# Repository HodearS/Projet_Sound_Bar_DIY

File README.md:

# Projet_Sound_Bar_DIY

L'objectif de ce projet est de réaliser une barre de son DIY compatible Dolby Atmos.
Pour cela, la barre de son exploitera des architectures de chez Texas Instruments, à la fois pour le processeur audio et la carte d'amplification.

Travaux à réaliser :
- Ajouter un processeur prenant en charge la communication Bluetooth et Wi-Fi.
- Trouver une méthode permettant de basculer entre différentes sources audio.
- Concevoir l'architecture globale du projet (gestion des différentes cartes, intégration dans le boîtier, etc.).
- Concevoir la carte d’alimentation.
- Concevoir la carte d’interface.

Travaux réalisés :
- Reprise du schéma de la carte d’évaluation EVMK2GX de Texas Instruments pour le processeur 66AK2G12 → Processeur_Barre_Son_Avant_Projet.
- Reprise du schéma de la carte amplificateur audio TIDA-01414 utilisant les amplificateurs TPA3244 → Amplificateur_Audio_Avant_Projet.
- Reprise du schéma de la carte fille audio K2G → Audio_Carte_fille.

The objective of this project is to build a DIY Dolby Atmos-compatible soundbar.
To achieve this, the soundbar will use Texas Instruments architectures for both the audio processor and the amplifier board.

Tasks to be completed :
- Add a processor supporting Bluetooth and Wi-Fi communication.
- Find a method to switch between different audio sources.
- Design the overall architecture of the project (management of the different boards, integration into the case, etc.).
- Design the power supply board.
- Design the interface board.

Completed tasks :
-Recreated the schematic of the Texas Instruments evaluation board EVMK2GX for the 66AK2G12 processor → Processeur_Barre_Son_Avant_Projet.
-Recreated the schematic of the audio amplifier board TIDA-01414 using TPA3244 amplifiers → Amplificateur_Audio_Avant_Projet.
-Recreated the schematic of the K2G audio daughter card → Audio_Carte_fille.

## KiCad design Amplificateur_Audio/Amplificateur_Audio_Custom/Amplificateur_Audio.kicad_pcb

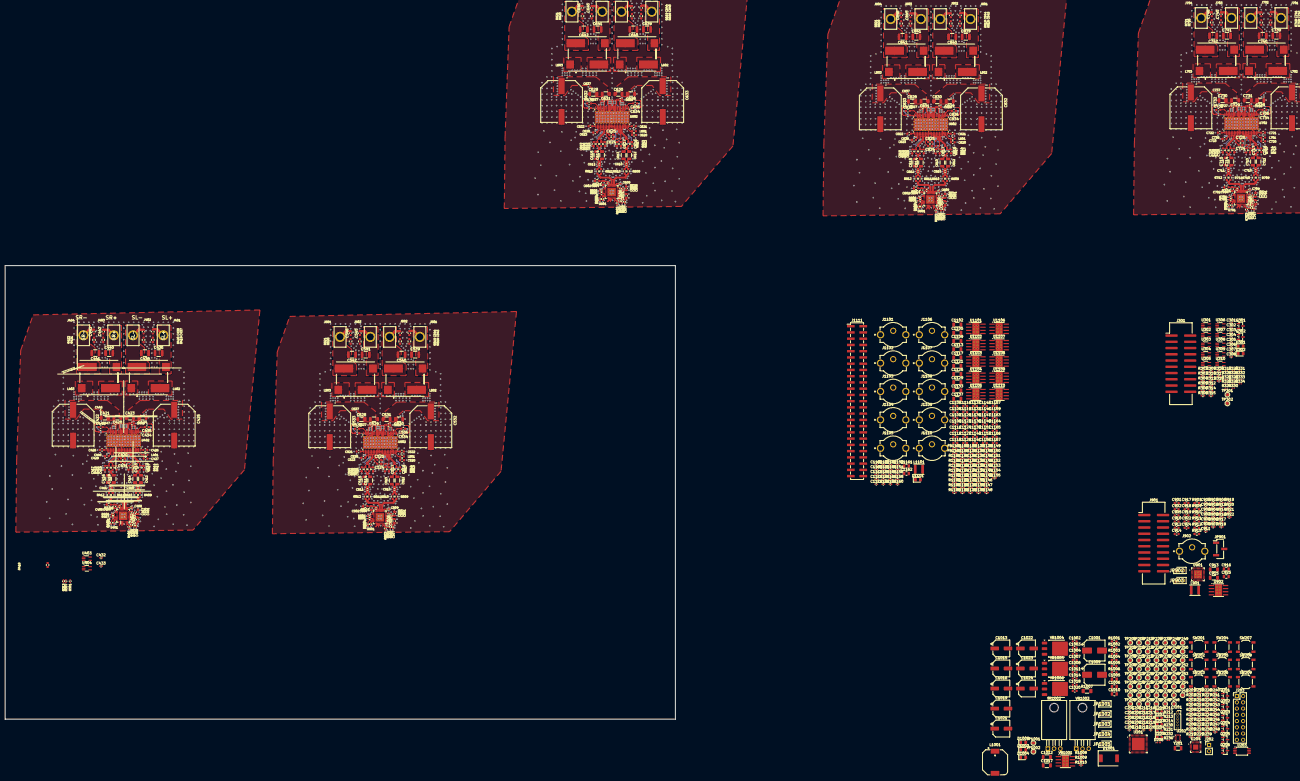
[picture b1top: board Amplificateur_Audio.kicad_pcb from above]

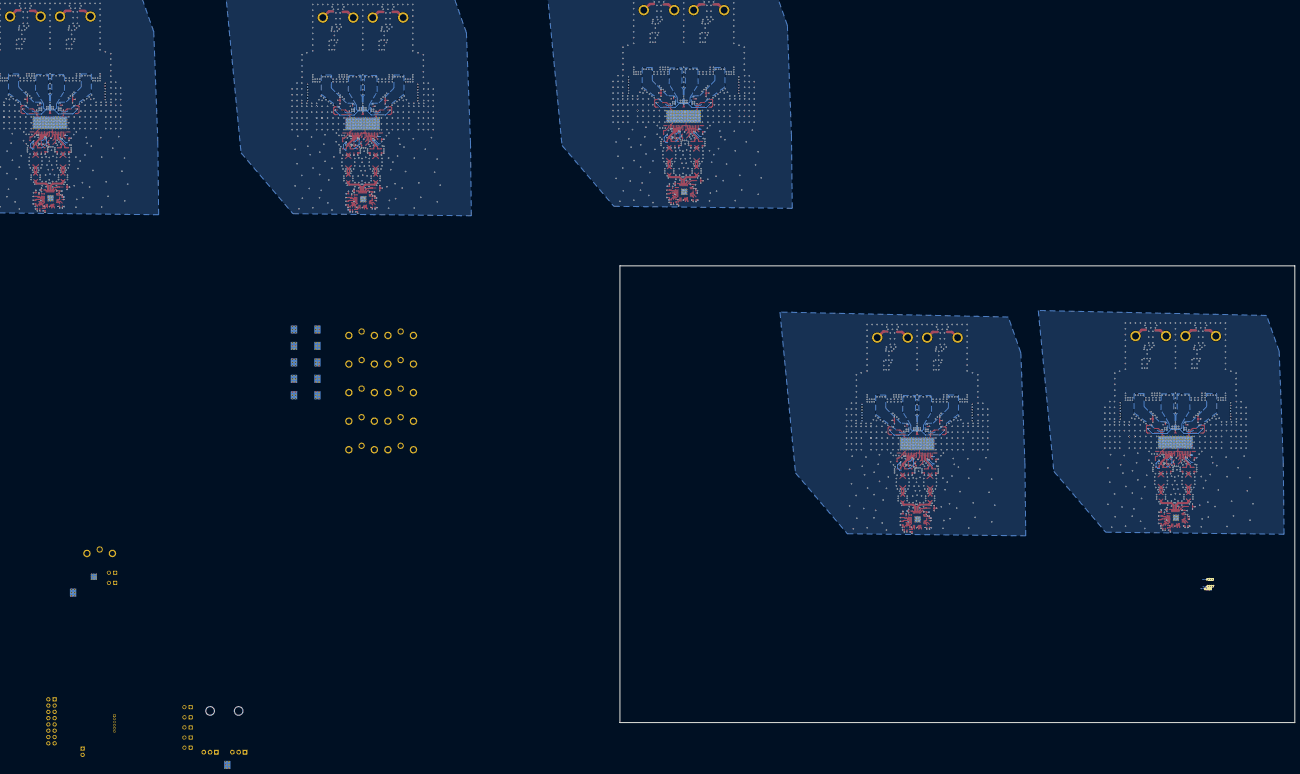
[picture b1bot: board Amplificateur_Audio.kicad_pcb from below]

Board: 4 copper layers, 272.5 x 184.4 mm, 847 parts (3 on the bottom side), 447 nets.

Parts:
C201, C202, C203, C204, C205, C206, C207, C208: 470pF; C_0402_1005Metric
C209, C301: 1uF; C_0402_1005Metric
C210, C211, C212, C213, C214, C215, C216, C302, C303, C304, C305, C306, C307, C308, C402, C404, C406, C409, C432, C433, C503, C504, C506, C507, C603, C604, C606, C607, C703, C704, C706, C707, C803, C804, C806, C807, C903, C904, C906, C908, C1101, C1106, C1110, C1114, C1118, C1122, C1126, C1130, C1134, C1138, C1142, C1144, C1146, C1148, C1150, C1152, C1154, C1156, C1158, C1160: 0.1uF; C_0402_1005Metric
C217, C218: 2200pF; C_0402_1005Metric
C219, C220: 12pF; C_0402_1005Metric
C401, C403, C405, C501, C502, C505, C601, C602, C605, C701, C702, C705, C801, C802, C805, C901, C902, C905, C914, C918, C922, C1141, C1143, C1145, C1147, C1149, C1151, C1153, C1155, C1157, C1159, C1164, C1165, C1166, C1167: 10uF; C_0603_1608Metric
C407, C408, C508, C509, C608, C609, C708, C709, C808, C809, C907, C909: 2.2uF; C_0402_1005Metric
C410, C411, C510, C511, C610, C611, C710, C711, C810, C811, C911: 1000pF; C_0402_1005Metric
C412, C414, C416, C418, C512, C513, C514, C515, C612, C613, C614, C615, C712, C713, C714, C715, C812, C813, C814, C815, C913, C915, C1102, C1105, C1109, C1113, C1117, C1121, C1125, C1129, C1133, C1137: 10uF; C_1206_3216Metric
C413, C415, C417, C419, C516, C517, C518, C519, C616, C617, C618, C619, C716, C717, C718, C719, C816, C817, C818, C819, C910, C912: 100pF; C_0603_1608Metric
C420, C421, C423, C424, C528, C529, C530, C531, C628, C629, C630, C631, C728, C729, C730, C731, C828, C829, C830, C831: 1uF; C_1206_3216Metric
C422, C425, C532, C533, C632, C633, C732, C733, C832, C833: 1000uF; CAP_EEVFK1H102M
C426, C427, C428, C446, C447, C448, C520, C521, C522, C526, C527, C538, C620, C621, C622, C626, C627, C638, C720, C721, C722, C726, C727, C738, C820, C821, C822, C826, C827, C838, C924, C1004, C1014, C1020, C1163: 0.1uF; C_0603_1608Metric
C429, C430, C523, C525, C623, C625, C723, C725, C823, C825, C1002: 1uF; C_0603_1608Metric
C431, C524, C624, C724, C824: 0.047uF; C_0603_1608Metric
C434, C435, C444, C445, C534, C535, C536, C537, C634, C635, C636, C637, C734, C735, C736, C737, C834, C835, C836, C837: 0.033uF; C_0603_1608Metric
C436, C438, C440, C441, C539, C540, C541, C542, C639, C640, C641, C642, C739, C740, C741, C742, C839, C840, C841, C842: 1uF; C_1210_3225Metric
C437, C439, C442, C443, C543, C544, C545, C546, C643, C644, C645, C646, C743, C744, C745, C746, C843, C844, C845, C846, C1003: 0.01uF; C_0603_1608Metric
C916, C925, C1161, C1162: 10uF; C_0805_2012Metric
C917, C919, C1103, C1104, C1107, C1108, C1111, C1112, C1115, C1116, C1119, C1120, C1123, C1124, C1127, C1128, C1131, C1132, C1135, C1136, C1139, C1140: 22pF; C_0603_1608Metric
C1001, C1009: 47uF; CP_Elec_8x6.2
C1005, C1006, C1010: 2.2uF; C_0805_2012Metric
C1007: 3600pF; C_0603_1608Metric
C1008: 75pF; C_0603_1608Metric
C1011, C1018: 0.47uF; C_0603_1608Metric
C1012, C1017: 4.7uF; C_1206_3216Metric
C1013, C1019: 47uF; CP_Elec_6.3x5.8
C1015, C1021, C1023: 10uF; CP_Elec_6.3x5.8
C1016, C1022, C1024: 100uF; CP_Elec_6.3x5.8
D201: MODE1; LED_0603_1608Metric_Pad1.05x0.95mm_HandSolder
D202: ACTIVITY; LED_0603_1608Metric_Pad1.05x0.95mm_HandSolder
D203: MODE2; LED_0603_1608Metric_Pad1.05x0.95mm_HandSolder
D204: MODE3; LED_0603_1608Metric_Pad1.05x0.95mm_HandSolder
D205: MODE4; LED_0603_1608Metric_Pad1.05x0.95mm_HandSolder
D206: MUTE; LED_0402_1005Metric_Pad0.77x0.64mm_HandSolder
D301: OTW (Orange); LED_0805_2012Metric_Pad1.15x1.40mm_HandSolder
D302: FAULT (Rouge); LED_0805_2012Metric_Pad1.15x1.40mm_HandSolder
D1001: 60V/5A; ST_D_SMC
D1002, D1003, D1004, D1101: GREEN; LED_0805_2012Metric_Pad1.15x1.40mm_HandSolder
FB1101, FB1102: 120E; R_0402_1005Metric_Pad0.72x0.64mm_HandSolder
J201: JTAG; PinSocket_1x06_P1.27mm_Vertical
J202: Conn_01x02; PinHeader_1x02_P2.54mm_Vertical
J203: Conn_02x08_Odd_Even; PinHeader_2x08_P2.54mm_Vertical
J301: Conn_02x10_Odd_Even; IDC-Header_2x10_P2.54mm_Vertical_SMD
J401, J501, J601, J701, J801: SL+; 630661MouserReel
J402, J502, J602, J702, J802: SL-; 630661MouserReel
J403, J503, J603, J703, J803: SR+; 630661MouserReel
J404, J504, J604, J704, J804: SR-; 630661MouserReel
J901: I2S-OUT; IDC-Header_2x10_P2.54mm_Vertical_SMD
J902: SUBOUT; CUI_RCJ-024
J1101: SURROUND-LEFT; CUI_RCJ-024
J1102: UPMIX-LEFT; CUI_RCJ-024
J1103: FR-TWEETER; CUI_RCJ-024
J1104: FL-TWEETER; CUI_RCJ-024
J1105: CENTER-TWEETER; CUI_RCJ-024
J1106: SURROUND-RIGHT; CUI_RCJ-024
J1107: UPMIX-RIGHT; CUI_RCJ-024
J1108: FR-WOOFER; CUI_RCJ-024
J1109: FL-WOOFER; CUI_RCJ-024
J1110: CENTER-WOOFER; CUI_RCJ-024
J1111: Analog OUTPUT Connector; PinHeader_2x25_P2.54mm_Vertical_SMD
JP901: DIN2-SEL; PinHeader_1x03_P2.54mm_Vertical_SMD_Pin1Left
JP902, JP903, JP1001, JP1002, JP1003, JP1004, JP1005: PBC02SAAN
L401, L501, L601, L701, L801: 10uH; L_0603_1608Metric
L402, L403, L502, L503, L602, L603, L702, L703, L802, L803: 10uH; UA8014ALD_Reverse
L901, L1101: 10uH; L_APV_ANR4012
L1001: 10uH; WE-PD_1050P
Q201, Q202, Q203, Q204, Q205, Q206: NPN; SOT-23
Q301, Q302: NMOS; SOT-23
R201, R202, R203, R204, R205, R206, R207, R208: 33.2k; R_0402_1005Metric_Pad0.72x0.64mm_HandSolder
R209, R903, R904, R906, R907, R908, R917, R918, R919, R920, R921, R922, R1101, R1103, R1104, R1105, R1107, R1108, R1109, R1110, R1112, R1113, R1114, R1115, R1117, R1118, R1119, R1120, R1122, R1123, R1124, R1125, R1127, R1128, R1129, R1130, R1132, R1133, R1134, R1135, R1137, R1138, R1139, R1140, R1142, R1143, R1144, R1145, R1147, R1148, R1149, R1150, R1152, R1153, R1154, R1155: 10k; R_0402_1005Metric_Pad0.72x0.64mm_HandSolder
R210, R211, R212, R213, R214, R236: 10k; R_0201_0603Metric_Pad0.64x0.40mm_HandSolder
R215, R216, R217, R218, R219, R220: 100; R_0402_1005Metric_Pad0.72x0.64mm_HandSolder
R221, R222, R223, R224, R225, R226: 2.15k; R_0402_1005Metric_Pad0.72x0.64mm_HandSolder
R227, R229: 47.5k; R_0402_1005Metric_Pad0.72x0.64mm_HandSolder
R228: 332; R_0402_1005Metric_Pad0.72x0.64mm_HandSolder
R230, R231, R232, R322, R323, R324, R325, R326, R327, R328, R329, R330, R331: 0; R_0201_0603Metric_Pad0.64x0.40mm_HandSolder
R233, R913, R914, R916, R1102, R1106, R1111, R1116, R1121, R1126, R1131, R1136, R1141, R1146: 100k; R_0402_1005Metric_Pad0.72x0.64mm_HandSolder
R234, R235, R237, R238, R239, R240, R241, R242, R243, R244, R245, R246, R247, R248: 2k; R_0402_1005Metric_Pad0.72x0.64mm_HandSolder
R301, R307, R313: 49.9; R_0402_1005Metric
R302, R303, R304, R305, R306, R308, R309, R310, R311, R312, R314, R315, R316, R317, R318: 49.9; R_0402_1005Metric_Pad0.72x0.64mm_HandSolder
R319, R334: 1k; R_0201_0603Metric_Pad0.64x0.40mm_HandSolder
R320, R333: 100; R_0201_0603Metric_Pad0.64x0.40mm_HandSolder
R321, R332: 47k; R_0201_0603Metric_Pad0.64x0.40mm_HandSolder
R401, R402, R504, R507, R604, R607, R704, R707, R804, R807: 4.99k; R_0402_1005Metric
R403, R404, R405, R406, R407, R502, R503, R505, R506, R508, R602, R603, R605, R606, R608, R702, R703, R705, R706, R708, R802, R803, R805, R806, R808: 10k; R_0402_1005Metric
R408, R501, R601, R701, R801: 10; R_0603_1608Metric
R409, R410, R411, R412, R509, R510, R511, R512, R609, R610, R611, R612, R709, R710, R711, R712, R809, R810, R811, R812, R911, R912: 499; R_0603_1608Metric_Pad0.98x0.95mm_HandSolder
R413, R414, R415, R416, R513, R514, R515, R516, R613, R614, R615, R616, R713, R714, R715, R716, R813, R814, R815, R816: 100; R_0603_1608Metric
R417, R517, R617, R717, R817: 22k; R_0603_1608Metric
R418: 30k; R_0603_1608Metric
R419, R420, R421, R422, R518, R519, R520, R521, R618, R619, R620, R621, R718, R719, R720, R721, R818, R819, R820, R821: 3.3; R_0603_1608Metric_Pad0.98x0.95mm_HandSolder
R901: 10; R_0603_1608Metric_Pad0.98x0.95mm_HandSolder
R902, R905: 4.99k; R_0402_1005Metric_Pad0.72x0.64mm_HandSolder
R909, R910: 100; R_0603_1608Metric_Pad0.98x0.95mm_HandSolder
R915: 49.9; R_0603_1608Metric_Pad0.98x0.95mm_HandSolder
R1001: 365k; R_0603_1608Metric_Pad0.98x0.95mm_HandSolder
R1002: 86.6k; R_0603_1608Metric_Pad0.98x0.95mm_HandSolder
R1003: 150k; R_0603_1608Metric_Pad0.98x0.95mm_HandSolder
R1004: 25.5k; R_0603_1608Metric_Pad0.98x0.95mm_HandSolder
R1005: 215k; R_0603_1608Metric_Pad0.98x0.95mm_HandSolder
R1006: 12.1k; R_0603_1608Metric_Pad0.98x0.95mm_HandSolder
R1007: 0; C_1206_3216Metric_Pad1.33x1.80mm_HandSolder
R1008, R1009, R1010: 360; C_0402_1005Metric_Pad0.74x0.62mm_HandSolder
R1151: 360; R_0402_1005Metric_Pad0.72x0.64mm_HandSolder
SW201: MUTE; SW_SPST_TL3342
SW202: VOL+; SW_SPST_TL3342
SW203: VOL-; SW_SPST_TL3342
SW204: MODE1; SW_SPST_TL3342
SW205: MODE2; SW_SPST_TL3342
SW206: MODE3; SW_SPST_TL3342
SW207: MODE4; SW_SPST_TL3342
SW208: LOAD; SW_SPST_TL3342
SW209: RESET; SW_SPST_TL3342
TP201: Mute; TestPoint_Pad_D1.5mm
TP202, TP211: GND; TestPoint_Pad_D1.5mm
TP203: VOL+; TestPoint_Pad_D1.5mm
TP204: VOL-; TestPoint_Pad_D1.5mm
TP205: MODE1; TestPoint_Pad_D1.5mm
TP206: MODE2; TestPoint_Pad_D1.5mm
TP207: MODE3; TestPoint_Pad_D1.5mm
TP208: MODE4; TestPoint_Pad_D1.5mm
TP209: LOAD; TestPoint_Pad_D1.5mm
TP210: U203 AO; TestPoint_Pad_D1.5mm
TP212: U203 VDD; TestPoint_Pad_D1.5mm
TP213: WP; TestPoint_Pad_D1.5mm
TP214: SCL; TestPoint_Pad_D1.5mm
TP215: SDA; TestPoint_Pad_D1.5mm
TP216: P5.5; TestPoint_Pad_D1.5mm
TP217: P5.4; TestPoint_Pad_D1.5mm
TP218: P6.0; TestPoint_Pad_D1.5mm
TP219: P6.1; TestPoint_Pad_D1.5mm
TP220: P6.2; TestPoint_Pad_D1.5mm
TP221: P6.3; TestPoint_Pad_D1.5mm
TP222: P6.4; TestPoint_Pad_D1.5mm
TP223: P6.5; TestPoint_Pad_D1.5mm
TP224: GND U201; TestPoint_Pad_D1.5mm
TP225: RESET; TestPoint_Pad_D1.5mm
TP226: AVCC U201; TestPoint_Pad_D1.5mm
TP227: SBWTDIO; TestPoint_Pad_D1.5mm
TP228: SBWTCK; TestPoint_Pad_D1.5mm
TP229: /AMP-RESET1; TestPoint_Pad_D1.5mm
TP230: /AMP-RESET2; TestPoint_Pad_D1.5mm
TP231: /AMP-RESET3; TestPoint_Pad_D1.5mm
TP232: /AMP-RESET4; TestPoint_Pad_D1.5mm
TP233: /AMP-RESET5; TestPoint_Pad_D1.5mm
TP234: VCC U202; TestPoint_Pad_D1.5mm
TP235: RESET U202; TestPoint_Pad_D1.5mm
TP236: GND U202; TestPoint_Pad_D1.5mm
TP237: SDA1; TestPoint_Pad_D1.5mm
TP238: SCL1; TestPoint_Pad_D1.5mm
TP239: SDA2; TestPoint_Pad_D1.5mm
TP240: SCL2; TestPoint_Pad_D1.5mm
TP241: SDA3; TestPoint_Pad_D1.5mm
TP242: SCL3; TestPoint_Pad_D1.5mm
TP243: SDA4; TestPoint_Pad_D1.5mm
TP244: SCL4; TestPoint_Pad_D1.5mm
TP245: SDA5; TestPoint_Pad_D1.5mm
TP246: SCL5; TestPoint_Pad_D1.5mm
TP247: SDA6; TestPoint_Pad_D1.5mm
TP248: SCL6; TestPoint_Pad_D1.5mm
TP249: SDA U202; TestPoint_Pad_D1.5mm
TP250: SCL U202; TestPoint_Pad_D1.5mm
TP251: VCC U204; TestPoint_Pad_D1.5mm
TP252: GDN U204; TestPoint_Pad_D1.5mm
TP253: RESET U204; TestPoint_Pad_D1.5mm
TP254: SCL U204; TestPoint_Pad_D1.5mm
TP255: SDA U204; TestPoint_Pad_D1.5mm
TP301: FAULT; TestPoint_Pad_D1.5mm
TP302: CLIP; TestPoint_Pad_D1.5mm
TP1001: PWR-IN; TestPoint_Pad_D1.5mm
TP1002: GND-IN; TestPoint_Pad_D1.5mm
U201: MSP430F5234IRGZ; Texas_RGZ0048A_VQFN-48-1EP_7x7mm_P0.5mm_EP5.15x5.15mm
U202: TCA6408ARSVR; QFN40P180X260X55-16N
U203: 24LC512; TSSOP-8_4.4x3mm_P0.65mm
U204: TCA9548ARGER; Texas_RGE0024C_VQFN-24-1EP_4x4mm_P0.5mm_EP2.1x2.1mm
U301, U302, U303, U304, U305, U306, U307, U308, U309, U310, U403, U404: 74LVC1G125; SOT-353_SC-70-5_Handsoldering
U401, U501, U601, U701, U801, U901: PCM5252RHBR; Texas_RHB0032E_VQFN-32-1EP_5x5mm_P0.5mm_EP3.45x3.45mm_Therm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
U402, U502, U602, U702, U802: TPA3244DDWR; HTSSOP-44-1EP_6.1x14mm_P0.635mm_EP5.2x14mm_Mask4.31x8.26mm_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
U902: NE5532; Texas_HTSOP-8-1EP_3.9x4.9mm_P1.27mm_EP2.95x4.9mm_Mask2.4x3.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
U1101, U1102, U1103, U1104, U1105, U1106, U1107, U1108, U1109, U1110: NE5532AD; Texas_HTSOP-8-1EP_3.9x4.9mm_P1.27mm_EP2.95x4.9mm_Mask2.4x3.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
VR1001: TPS54340DDAR; Texas_HTSOP-8-1EP_3.9x4.9mm_P1.27mm_EP2.95x4.9mm_Mask2.4x3.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
VR1002, VR1003: LM2940CT-12/NOPB; TO-220-3_Horizontal_TabDown
VR1004, VR1005, VR1006: TLV1117-33IKVURG3; TO-252-3_TabPin4
Y201: 32.768kHz; Crystal_SMD_3215-2Pin_3.2x1.5mm

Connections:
3.3V: JP1001.2 (B), JP1002.1 (A)
3.3V-1: C1022.1, D1003.2 (A), JP1005.1 (A), VR1005.4 (OUT)
3.3V-2: C1024.1, D1004.2 (A), VR1006.4 (OUT)
3.3V-3: C209.2, C210.2, C211.2, C212.2, C301.2, C302.2, C303.2, C304.2, C305.2, C306.2, C307.2, C308.2, JP1002.2 (B), R209.2, R236.2, R237.1, R238.1, R239.1, R240.1, R241.1, R242.1, R243.1, R244.1, R245.1, R246.1, R247.1, R248.1, R321.1, R332.1, TP234.1, TP251.1, U202.14 (VCCP), U202.15 (VCCI), U204.21 (VCC), U301.5 (VCC), U302.5 (VCC), U303.5 (VCC), U304.5 (VCC), U305.5 (VCC), U306.5 (VCC), U307.5 (VCC), U308.5 (VCC), U309.5 (VCC), U310.5 (VCC)
3.3V-4: C401.2, C402.2, C403.2, C406.2, C432.2, C433.2, C501.2, C503.2, C505.2, C506.2, C601.2, C603.2, C605.2, C606.2, C701.2, C703.2, C705.2, C706.2, C801.2, C803.2, C805.2, C806.2, JP1005.2 (B), R402.1, R403.1, R406.2, R407.2, R408.2, R501.2, R502.2, R505.2, R507.1, R508.1, R601.2, R602.2, R605.2, R607.1, R608.1, R701.2, R702.2, R705.2, R707.1, R708.1, R801.2, R802.2, R805.2, R807.1, R808.1, U401.4 (DVDD), U401.5 (CPVDD), U403.5 (VCC), U404.5 (VCC), U501.4 (DVDD), U501.5 (CPVDD), U601.4 (DVDD), U601.5 (CPVDD), U701.4 (DVDD), U701.5 (CPVDD), U801.4 (DVDD), U801.5 (CPVDD)
3.3V-IO: D1101.2 (A), J1111.6, J1111.8
3.3V-VR6: C1016.1, D1002.2 (A), JP1001.1 (A), VR1004.4 (OUT)
3V3: C213.2, C214.2, C215.2, C216.2, C901.2, C903.2, C905.2, C906.2, J202.1, R201.2, R202.2, R203.2, R204.2, R205.2, R206.2, R207.2, R208.2, R215.2, R216.2, R217.2, R218.2, R219.2, R220.2, R227.2, R229.1, R230.2, R233.1, R234.1, R235.1, R901.2, R903.2, R905.1, R906.2, R908.2, TP212.1, TP226.1, U201.6 (AVCC), U201.10 (DVCC), U201.12 (VCORE), U201.28 (DVCC), U203.8 (VDD), U901.4 (DVDD), U901.5 (CPVDD)
12V: C426.2, C428.2, C521.2, C522.2, C621.2, C622.2, C721.2, C722.2, C821.2, C822.2, JP1003.1 (A), L401.1, L501.1, L601.1, L701.1, L801.1, L901.1, R319.2, R334.2, R1007.1, U402.1 (GVDD_CD), U402.22 (GVDD_AB), U502.1 (GVDD_CD), U502.22 (GVDD_AB), U602.1 (GVDD_CD), U602.22 (GVDD_AB), U702.1 (GVDD_CD), U702.22 (GVDD_AB), U802.1 (GVDD_CD), U802.22 (GVDD_AB)
12V-IO: J1111.2, J1111.4, L1101.1
12V-OA: C916.2, C924.2, C925.2, L901.2, R921.2, U902.8 (V+)
12V-OA-IO: C1141.2, C1142.2, C1143.2, C1144.2, C1145.2, C1146.2, C1147.2, C1148.2, C1149.2, C1150.2, C1151.2, C1152.2, C1153.2, C1154.2, C1155.2, C1156.2, C1157.2, C1158.2, C1159.2, C1160.2, C1161.2, C1162.2, C1163.2, L1101.2, R1153.2, R1154.2, U1101.8 (V+), U1102.8 (V+), U1103.8 (V+), U1104.8 (V+), U1105.8 (V+), U1106.8 (V+), U1107.8 (V+), U1108.8 (V+), U1109.8 (V+), U1110.8 (V+)
15V: C1009.1, C1010.1, C1011.1, C1012.1, C1017.1, C1018.1, L1001.2, R1005.1, VR1002.1 (IN), VR1003.1 (IN)
/Center_Hierarchy/DACFL+: C812.2, R813.2
/Center_Hierarchy/DACFL-: C813.2, R814.2
/Center_Hierarchy/DACFR+: C815.2, R816.2
/Center_Hierarchy/DACFR-: C814.2, R815.2
/Center_Hierarchy/DACL+: C810.1, C812.1, R809.1
/Center_Hierarchy/DACL-: C810.2, C813.1, R810.1
/Center_Hierarchy/DACR+: C811.2, C815.1, R812.1
/Center_Hierarchy/DACR-: C811.1, C814.1, R811.1
/Center_Hierarchy/Freq_ADJ_1: C823.1, U802.12 (DVDD), U802.15 (FREQ_ADJ)
/Clock_Drivers//CLIP_OTW: R320.2, R321.2, R322.1, R323.1, R324.1, R325.1, R326.1, TP302.1
/Clock_Drivers//FAULT: R327.1, R328.1, R329.1, R330.1, R331.1, R332.2, R333.2, TP301.1
/DIN0: U601.28 (DIN), U701.28 (DIN)
/Front_Left_Hierarchy/DACFL+: C712.2, R713.2
/Front_Left_Hierarchy/DACFL-: C713.2, R714.2
/Front_Left_Hierarchy/DACFR+: C715.2, R716.2
/Front_Left_Hierarchy/DACFR-: C714.2, R715.2
/Front_Left_Hierarchy/DACL+: C710.1, C712.1, R709.1
/Front_Left_Hierarchy/DACL-: C710.2, C713.1, R710.1
/Front_Left_Hierarchy/DACR+: C711.2, C715.1, R712.1
/Front_Left_Hierarchy/DACR-: C711.1, C714.1, R711.1
/Front_Left_Hierarchy/Freq_ADJ_1: C723.1, U702.12 (DVDD), U702.15 (FREQ_ADJ)
/Front_Right_Hierarchy/DACFL+: C612.2, R613.2
/Front_Right_Hierarchy/DACFL-: C613.2, R614.2
/Front_Right_Hierarchy/DACFR+: C615.2, R616.2
/Front_Right_Hierarchy/DACFR-: C614.2, R615.2
/Front_Right_Hierarchy/DACL+: C610.1, C612.1, R609.1
/Front_Right_Hierarchy/DACL-: C610.2, C613.1, R610.1
/Front_Right_Hierarchy/DACR+: C611.2, C615.1, R612.1
/Front_Right_Hierarchy/DACR-: C611.1, C614.1, R611.1
/Front_Right_Hierarchy/Freq_ADJ_1: C623.1, U602.12 (DVDD), U602.15 (FREQ_ADJ)
/INPUTL1+: C413.1, R413.1, U402.18 (INPUT_A)
/INPUTL1-: C415.1, R414.1, U402.17 (INPUT_B)
/INPUTL2+: C516.1, R513.1, U502.18 (INPUT_A)
/INPUTL2-: C517.1, R514.1, U502.17 (INPUT_B)
/INPUTL3+: C616.1, R613.1, U602.18 (INPUT_A)
/INPUTL3-: C617.1, R614.1, U602.17 (INPUT_B)
/INPUTL4+: C716.1, R713.1, U702.18 (INPUT_A)
/INPUTL4-: C717.1, R714.1, U702.17 (INPUT_B)
/INPUTL5+: C816.1, R813.1, U802.18 (INPUT_A)
/INPUTL5-: C817.1, R814.1, U802.17 (INPUT_B)
/INPUTR1+: C417.1, R415.1, U402.6 (INPUT_D)
/INPUTR1-: C419.1, R416.1, U402.7 (INPUT_C)
/INPUTR2+: C519.1, R516.1, U502.6 (INPUT_D)
/INPUTR2-: C518.1, R515.1, U502.7 (INPUT_C)
/INPUTR3+: C619.1, R616.1, U602.6 (INPUT_D)
/INPUTR3-: C618.1, R615.1, U602.7 (INPUT_C)
/INPUTR4+: C719.1, R716.1, U702.6 (INPUT_D)
/INPUTR4-: C718.1, R715.1, U702.7 (INPUT_C)
/INPUTR5+: C819.1, R816.1, U802.6 (INPUT_D)
/INPUTR5-: C818.1, R815.1, U802.7 (INPUT_C)
/MSP43_IO/P5.4: C219.2, TP217.1, U201.7 (P5.4/XIN), Y201.1
/MSP43_IO/P5.5: C220.2, TP216.1, U201.8 (P5.5/XOUT), Y201.2
/MSP43_IO/P6.0: R225.2, TP218.1, U201.46 (P6.0/CB0)
/MSP43_IO/P6.1: R221.2, TP219.1, U201.47 (P6.1/CB1)
/MSP43_IO/P6.2: R222.2, TP220.1, U201.48 (P6.2/CB2)
/MSP43_IO/P6.3: R226.2, TP221.1, U201.1 (P6.3/CB3)
/MSP43_IO/P6.4: R224.2, TP222.1, U201.2 (P6.4/CB4)
/MSP43_IO/P6.5: R223.2, TP223.1, U201.3 (P6.5/CB5)
/MSP43_IO/SBWTCK: R228.2, TP228.1, U201.40 (SBWTCK/TEST)
/MSP43_IO/SBWTDIO: C218.1, J201.3, R229.2, TP227.1, U201.45 (~RSTDVCC/SBWTDIO)
/MSP43_IO/TCK: J201.4, R228.1
/MSP43_IO//RESET: C217.1, R227.1, SW209.1, TP225.1, U201.37 (~RST/NMI)
/Power_Supplies/12-VR2: C1013.1, C1014.1, C1015.1, R1007.2, VR1002.3 (OUT), VR1004.3 (IN)
/Power_Supplies/12V-VR3: C1019.1, C1020.1, C1021.1, C1023.1, VR1003.3 (OUT), VR1005.3 (IN), VR1006.3 (IN)
/Power_Supplies/SW-VR1: C1004.2, D1001.1 (K), L1001.1, VR1001.8 (SW)
/Subwoofer_Channel/SCL7: JP902.2 (B), U901.18 (MC/SCL/ATT1)
/Subwoofer_Channel/SDA7: JP903.2 (B), U901.17 (MOSI/SDA/ATT2)
/Surround_Hierarchy/DACFL+: C412.2, R413.2
/Surround_Hierarchy/DACFL-: C414.2, R414.2
/Surround_Hierarchy/DACFR+: C416.2, R415.2
/Surround_Hierarchy/DACFR-: C418.2, R416.2
/Surround_Hierarchy/DACL+: C410.1, C412.1, R409.1
/Surround_Hierarchy/DACL-: C410.2, C414.1, R410.1
/Surround_Hierarchy/DACR+: C411.2, C416.1, R412.1
/Surround_Hierarchy/DACR-: C411.1, C418.1, R411.1
/Surround_Hierarchy/Freq_ADJ_1: C429.1, U402.12 (DVDD), U402.15 (FREQ_ADJ)
/Up_Hierarchy/DACFL+: C512.2, R513.2
/Up_Hierarchy/DACFL-: C513.2, R514.2
/Up_Hierarchy/DACFR+: C515.2, R516.2
/Up_Hierarchy/DACFR-: C514.2, R515.2
/Up_Hierarchy/DACL+: C510.1, C512.1, R509.1
/Up_Hierarchy/DACL-: C510.2, C513.1, R510.1
/Up_Hierarchy/DACR+: C511.2, C515.1, R512.1
/Up_Hierarchy/DACR-: C511.1, C514.1, R511.1
/Up_Hierarchy/Freq_ADJ_1: C523.1, U502.12 (DVDD), U502.15 (FREQ_ADJ)
BCK6: J901.3, R312.2, U901.27 (BCK)
CT+: C1119.2, J1111.44, R1123.2, R1124.2, U1105.1
CT-: C1120.2, J1111.46, R1125.2, U1105.7
CW+: C1139.2, J1111.48, R1148.2, R1149.2, U1110.1
CW-: C1140.2, J1111.50, R1150.2, U1110.7
DIN2: JP901.2 (C), U309.4, U901.28 (DIN)
DSP-BCLK: J301.4, U303.2, U304.2
DSP-DATA0: J301.8, U307.2
DSP-DATA1: J301.10, U308.2
DSP-DATA2: J301.12, U309.2
DSP-DATA3: J301.14, U310.2
DSP-LRCLK: J301.2, U301.2, U302.2
DSP-MCLK: J301.6, U305.2, U306.2
FLT+: C1115.2, J1111.36, R1118.2, R1119.2, U1104.1
FLT-: C1116.2, J1111.38, R1120.2, U1104.7
FLW+: C1135.2, J1111.40, R1143.2, R1144.2, U1109.1
FLW-: C1136.2, J1111.42, R1145.2, U1109.7
FRT+: C1111.2, J1111.28, R1113.2, R1114.2, U1103.1
FRT-: C1112.2, J1111.30, R1115.2, U1103.7
FRW+: C1131.2, J1111.32, R1138.2, R1139.2, U1108.1
FRW-: C1132.2, J1111.34, R1140.2, U1108.7
GND: C201.1, C202.1, C203.1, C204.1, C205.1, C206.1, C207.1, C208.1, C209.1, C210.1, C211.1, C212.1, C213.1, C214.1, C215.1, C216.1, C217.2, C218.2, C219.1, C220.1, C301.1, C302.1, C303.1, C304.1, C305.1, C306.1, C307.1, C308.1, C401.1, C402.1, C403.1, C404.1, C405.1, C406.1, C408.2, C409.2, C413.2, C415.2, C417.2, C419.2, C420.1, C421.1, C422.2, C423.1, C424.1, C425.2, C426.1, C427.1, C428.1, C429.2, C430.2, C431.1, C432.1, C433.1, C436.1, C438.1, C440.1, C441.1, C446.1, C447.1, C448.1, C501.1, C502.1, C503.1, C504.1, C505.1, C506.1, C507.2, C509.2, C516.2, C517.2, C518.2, C519.2, C520.1, C521.1, C522.1, C523.2, C524.1, C525.2, C526.1, C527.1, C528.1, C529.1, C530.1, C531.1, C532.2, C533.2, C538.1, C539.1, C540.1, C541.1, C542.1, C601.1, C602.1, C603.1, C604.1, C605.1, C606.1, C607.2, C609.2, C616.2, C617.2, C618.2, C619.2, C620.1, C621.1, C622.1, C623.2, C624.1, C625.2, C626.1, C627.1, C628.1, C629.1, C630.1, C631.1, C632.2, C633.2, C638.1, C639.1, C640.1, C641.1, C642.1, C701.1, C702.1, C703.1, C704.1, C705.1, C706.1, C707.2, C709.2, C716.2, C717.2, C718.2, C719.2, C720.1, C721.1, C722.1, C723.2, C724.1, C725.2, C726.1, C727.1, C728.1, C729.1, C730.1, C731.1, C732.2, C733.2, C738.1, C739.1, C740.1, C741.1, C742.1, C801.1, C802.1, C803.1, C804.1, C805.1, C806.1, C807.2, C809.2, C816.2, C817.2, C818.2, C819.2, C820.1, C821.1, C822.1, C823.2, C824.1, C825.2, C826.1, C827.1, C828.1, C829.1, C830.1, C831.1, C832.2, C833.2, C838.1, C839.1, C840.1, C841.1, C842.1, C901.1, C902.1, C903.1, C904.1, C905.1, C906.1, C908.1, C909.2, C910.2, C912.2, C916.1, C918.2, C922.2, C924.1, C925.1, C1001.2, C1002.2, C1003.2, C1005.2, C1006.2, C1007.2, C1008.2, C1009.2, C1010.2, C1011.2, C1012.2, C1013.2, C1014.2, C1015.2, C1016.2, C1017.2, C1018.2, C1019.2, C1020.2, C1021.2, C1022.2, C1023.2, C1024.2, D301.1 (K), D302.1 (K), D1001.2 (A), FB1102.1, J201.2, J203.4, J203.6, J203.8, J203.10, J203.12, J301.1, J301.3, J301.5, J301.7, J301.9, J301.11, J301.13, J301.15, J301.17, J301.19, J901.10, Q201.3 (E), Q202.3 (E), Q203.3 (E), Q204.3 (E), Q205.3 (E), Q206.3 (E), Q301.3 (S), Q302.3 (S), R210.1, R211.1, R212.1, R213.1, R214.1, R231.1, R232.1, R401.1, R404.1, R405.1, R417.2, R418.2, R419.2, R420.2, R421.2, R422.2, R503.1, R504.1, R506.1, R517.2, R518.2, R519.2, R520.2, R521.2, R603.1, R604.1, R606.1, R617.2, R618.2, R619.2, R620.2, R621.2, R703.1, R704.1, R706.1, R717.2, R718.2, R719.2, R720.2, R721.2, R803.1, R804.1, R806.1, R817.2, R818.2, R819.2, R820.2, R821.2, R902.1, R904.1, R907.1, R913.2, R914.2, R916.2, R922.1, R1002.2, R1003.2, R1006.2, R1008.2, R1009.2, R1010.2, SW201.1, SW202.1, SW203.1, SW204.1, SW205.1, SW206.1, SW207.1, SW208.1, SW209.2, TP202.1, TP211.1, TP224.1, TP236.1, TP252.1, TP1002.1, U201.9 (AVSS), U201.11 (DVSS), U201.27 (DVSS), U201.49 (PAD), U202.6 (GND), U202.16 (ADDR), U203.2 (A1), U203.3 (A2), U203.4 (VSS), U204.9 (GND), U204.18 (A2), U204.22 (A0), U204.23 (A1), U204.25 (PAD), U301.1, U301.3 (GND), U302.1, U302.3 (GND), U303.1, U303.3 (GND), U304.1, U304.3 (GND), U305.1, U305.3 (GND), U306.1, U306.3 (GND), U307.1, U307.3 (GND), U308.1, U308.3 (GND), U309.1, U309.3 (GND), U310.1, U310.3 (GND), U401.3 (DGND), U401.7 (CPGND), U401.15 (AGND), U401.33 (GND), U402.10 (GND), U402.11 (GND), U402.19 (M2), U402.20 (M1), U402.25 (GND), U402.26 (GND), U402.33 (GND), U402.34 (GND), U402.41 (GND), U402.42 (GND), U402.45 (PowerPAD), U403.1, U403.3 (GND), U404.1, U404.3 (GND), U501.3 (DGND), U501.7 (CPGND), U501.15 (AGND), U501.33 (GND), U502.10 (GND), U502.11 (GND), U502.19 (M2), U502.20 (M1), U502.25 (GND), U502.26 (GND), U502.33 (GND), U502.34 (GND), U502.41 (GND), U502.42 (GND), U502.45 (PowerPAD), U601.3 (DGND), U601.7 (CPGND), U601.15 (AGND), U601.33 (GND), U602.10 (GND), U602.11 (GND), U602.19 (M2), U602.20 (M1), U602.25 (GND), U602.26 (GND), U602.33 (GND), U602.34 (GND), U602.41 (GND), U602.42 (GND), U602.45 (PowerPAD), U701.3 (DGND), U701.7 (CPGND), U701.15 (AGND), U701.33 (GND), U702.10 (GND), U702.11 (GND), U702.19 (M2), U702.20 (M1), U702.25 (GND), U702.26 (GND), U702.33 (GND), U702.34 (GND), U702.41 (GND), U702.42 (GND), U702.45 (PowerPAD), U801.3 (DGND), U801.7 (CPGND), U801.15 (AGND), U801.33 (GND), U802.10 (GND), U802.11 (GND), U802.19 (M2), U802.20 (M1), U802.25 (GND), U802.26 (GND), U802.33 (GND), U802.34 (GND), U802.41 (GND), U802.42 (GND), U802.45 (PowerPAD), U901.3 (DGND), U901.7 (CPGND), U901.15 (AGND), U901.33 (GND), U902.4 (V-), VR1001.7 (GND), VR1001.9 (PAD), VR1002.2 (GND), VR1003.2 (GND), VR1004.1 (GND), VR1005.1 (GND), VR1006.1 (GND)
GND-IO: C1101.2, C1106.2, C1110.2, C1114.2, C1118.2, C1122.2, C1126.2, C1130.2, C1134.2, C1138.2, C1141.1, C1142.1, C1143.1, C1144.1, C1145.1, C1146.1, C1147.1, C1148.1, C1149.1, C1150.1, C1151.1, C1152.1, C1153.1, C1154.1, C1155.1, C1156.1, C1157.1, C1158.1, C1159.1, C1160.1, C1161.1, C1162.1, C1163.1, C1164.1, C1165.1, C1166.1, C1167.1, FB1101.2, FB1102.2, J1101.2, J1102.2, J1103.2, J1104.2, J1105.2, J1106.2, J1107.2, J1108.2, J1109.2, J1110.2, J1111.1, J1111.3, J1111.5, J1111.7, J1111.9, J1111.11, J1111.13, J1111.15, J1111.17, J1111.19, J1111.21, J1111.23, J1111.25, J1111.27, J1111.29, J1111.31, J1111.33, J1111.35, J1111.37, J1111.39, J1111.41, J1111.43, J1111.45, J1111.47, J1111.49, R1102.1, R1106.1, R1111.1, R1116.1, R1121.1, R1126.1, R1131.1, R1136.1, R1141.1, R1146.1, R1151.2, R1152.1, R1155.1, U1101.4 (V-), U1102.4 (V-), U1103.4 (V-), U1104.4 (V-), U1105.4 (V-), U1106.4 (V-), U1107.4 (V-), U1108.4 (V-), U1109.4 (V-), U1110.4 (V-)
LRCK6: J901.7, R306.2, U901.31 (LRCK)
unnamed: C434.1, L402.4, U402.27 (OUT_A), U402.28 (OUT_A)
unnamed: C437.1, R419.1
unnamed: C439.1, R420.1
unnamed: C442.1, R421.1
unnamed: C443.1, R422.1
unnamed: C445.1, L403.1, U402.39 (OUT_D), U402.40 (OUT_D)
unnamed: C534.1, L502.4, U502.27 (OUT_A), U502.28 (OUT_A)
unnamed: C537.1, L503.1, U502.39 (OUT_D), U502.40 (OUT_D)
unnamed: C543.1, R518.1
unnamed: C544.1, R519.1
unnamed: C545.1, R520.1
unnamed: C546.1, R521.1
unnamed: C634.1, L602.4, U602.27 (OUT_A), U602.28 (OUT_A)
unnamed: C637.1, L603.1, U602.39 (OUT_D), U602.40 (OUT_D)
unnamed: C643.1, R618.1
unnamed: C644.1, R619.1
unnamed: C645.1, R620.1
unnamed: C646.1, R621.1
unnamed: C734.1, L702.4, U702.27 (OUT_A), U702.28 (OUT_A)
unnamed: C737.1, L703.1, U702.39 (OUT_D), U702.40 (OUT_D)
unnamed: C743.1, R718.1
unnamed: C744.1, R719.1
unnamed: C745.1, R720.1
unnamed: C746.1, R721.1
unnamed: C834.1, L802.4, U802.27 (OUT_A), U802.28 (OUT_A)
unnamed: C837.1, L803.1, U802.39 (OUT_D), U802.40 (OUT_D)
unnamed: C843.1, R818.1
unnamed: C844.1, R819.1
unnamed: C845.1, R820.1
unnamed: C846.1, R821.1
unnamed: C910.1, C913.1, R909.1, R913.1
unnamed: C911.1, R909.2, R911.1
unnamed: C911.2, R910.2, R912.1
unnamed: C912.1, C915.1, R910.1, R914.1
unnamed: C913.2, R918.2
unnamed: C914.1, R915.1
unnamed: C914.2, R916.1
unnamed: C915.2, R919.2
unnamed: C917.2, R915.2, R917.1, U902.1
unnamed: C1007.1, R1004.2
unnamed: C1102.1, R1101.1
unnamed: C1102.2, R1102.2
unnamed: C1105.1, R1107.1
unnamed: C1105.2, R1106.2
unnamed: C1109.1, R1112.1
unnamed: C1109.2, R1111.2
unnamed: C1113.1, R1117.1
unnamed: C1113.2, R1116.2
unnamed: C1117.1, R1122.1
unnamed: C1117.2, R1121.2
unnamed: C1121.1, R1127.1
unnamed: C1121.2, R1126.2
unnamed: C1125.1, R1132.1
unnamed: C1125.2, R1131.2
unnamed: C1129.1, R1137.1
unnamed: C1129.2, R1136.2
unnamed: C1133.1, R1142.1
unnamed: C1133.2, R1141.2
unnamed: C1137.1, R1147.1
unnamed: C1137.2, R1146.2
unnamed: D201.2 (A), R217.1
unnamed: D201.1 (K), Q201.1 (C)
unnamed: D202.2 (A), R215.1
unnamed: D202.1 (K), Q202.1 (C)
unnamed: D203.2 (A), R218.1
unnamed: D203.1 (K), Q203.1 (C)
unnamed: D204.2 (A), R219.1
unnamed: D204.1 (K), Q204.1 (C)
unnamed: D205.2 (A), R216.1
unnamed: D205.1 (K), Q205.1 (C)
unnamed: D206.2 (A), R220.1
unnamed: D206.1 (K), Q206.1 (C)
unnamed: D301.2 (A), Q301.1 (D), R319.1
unnamed: D302.2 (A), Q302.1 (D), R334.1
unnamed: D1002.1 (K), R1010.1
unnamed: D1003.1 (K), R1009.1
unnamed: D1004.1 (K), R1008.1
unnamed: D1101.1 (K), R1151.1
unnamed: J201.5, J202.2
unnamed: C436.2, C437.2, J401.1, L402.3
unnamed: C438.2, C439.2, J402.1, L402.2
unnamed: C440.2, C442.2, J403.1, L403.3
unnamed: C441.2, C443.2, J404.1, L403.2
unnamed: C539.2, C543.2, J501.1, L502.3
unnamed: C540.2, C544.2, J502.1, L502.2
unnamed: C541.2, C545.2, J503.1, L503.3
unnamed: C542.2, C546.2, J504.1, L503.2
unnamed: C639.2, C643.2, J601.1, L602.3
unnamed: C640.2, C644.2, J602.1, L602.2
unnamed: C641.2, C645.2, J603.1, L603.3
unnamed: C642.2, C646.2, J604.1, L603.2
unnamed: C739.2, C743.2, J701.1, L702.3
unnamed: C740.2, C744.2, J702.1, L702.2
unnamed: C741.2, C745.2, J703.1, L703.3
unnamed: C742.2, C746.2, J704.1, L703.2
unnamed: C839.2, C843.2, J801.1, L802.3
unnamed: C840.2, C844.2, J802.1, L802.2
unnamed: C841.2, C845.2, J803.1, L803.3
unnamed: C842.2, C846.2, J804.1, L803.2
unnamed: J901.11, JP901.1 (A)
unnamed: J901.13, JP901.3 (B)
unnamed: JP1003.2 (B), JP1004.1 (A)
unnamed: Q201.2 (B), R223.1
unnamed: Q202.2 (B), R221.1
unnamed: Q203.2 (B), R224.1
unnamed: Q204.2 (B), R226.1
unnamed: Q205.2 (B), R222.1
unnamed: Q206.2 (B), R225.1
unnamed: Q301.2 (G), R320.1
unnamed: Q302.2 (G), R333.1
unnamed: R301.1, R302.1, R303.1, U301.4
unnamed: R304.1, R305.1, R306.1, U302.4
unnamed: R307.1, R308.1, R309.1, U303.4
unnamed: R310.1, R311.1, R312.1, U304.4
unnamed: R313.1, R314.1, R315.1, U305.4
unnamed: R316.1, R317.1, R318.1, U306.4
unnamed: C207.2, R207.1, SW207.2, TP208.1, U201.19 (CBOUT/TA1CLK/P1.6)
unnamed: C202.2, R202.1, SW202.2, TP203.1, U201.14 (TA0.0/P1.1)
unnamed: C203.2, R203.1, SW203.2, TP204.1, U201.15 (TA0.1/P1.2)
unnamed: C204.2, R204.1, SW204.2, TP205.1, U201.16 (TA0.2/P1.3)
unnamed: C205.2, R205.1, SW205.2, TP206.1, U201.17 (TA0.3/P1.4)
unnamed: C206.2, R206.1, SW206.2, TP207.1, U201.18 (TA0.4/P1.5)
unnamed: C201.2, R201.1, SW201.2, TP201.1, U201.13 (TA0CLK/ACLK/P1.0)
unnamed: C208.2, R208.1, SW208.2, TP209.1, U201.20 (TA1.0/P1.7)
unnamed: R209.1, TP235.1, U202.1 (~RESET)
unnamed: R230.1, R231.2, TP210.1, U203.1 (A0)
unnamed: R232.2, R233.2, TP213.1, U203.7 (WP)
unnamed: R236.1, TP253.1, U204.24 (~RESET)
unnamed: C404.2, C405.2, R408.1, U401.14 (AVDD)
unnamed: C407.2, U401.8 (CAPM)
unnamed: C407.1, U401.6 (CAPP)
unnamed: R404.2, R407.1, U401.22 (GPIO2/ADR2/GPO)
unnamed: C409.1, U401.2 (LDOO)
unnamed: R405.2, R406.1, U401.32 (MISO(GPIO1)/ADR1/FMT)
unnamed: R401.2, U401.23 (MODE1)
unnamed: R402.2, U401.24 (MS/MODE2)
unnamed: R410.2, U401.11 (OUTLN)
unnamed: R409.2, U401.10 (OUTLP)
unnamed: R411.2, U401.12 (OUTRN)
unnamed: R412.2, U401.13 (OUTRP)
unnamed: C408.1, U401.9 (VNEG)
unnamed: R403.2, U401.1 (XSMT)
unnamed: C430.1, U402.9 (AVDD)
unnamed: C434.2, U402.23 (BST_A)
unnamed: C435.2, U402.24 (BST_B)
unnamed: C444.2, U402.43 (BST_C)
unnamed: C445.2, U402.44 (BST_D)
unnamed: C431.2, U402.8 (C_START)
unnamed: R417.1, U402.16 (OC_ADJ)
unnamed: C435.1, L402.1, U402.32 (OUT_B)
unnamed: C444.1, L403.4, U402.35 (OUT_C)
unnamed: C446.2, U402.3 (VBG)
unnamed: C427.2, L401.2, U402.21 (VDD)
unnamed: C502.2, C504.2, R501.1, U501.14 (AVDD)
unnamed: C508.2, U501.8 (CAPM)
unnamed: C508.1, U501.6 (CAPP)
unnamed: R505.1, R506.2, U501.22 (GPIO2/ADR2/GPO)
unnamed: C507.1, U501.2 (LDOO)
unnamed: R502.1, R503.2, U501.32 (MISO(GPIO1)/ADR1/FMT)
unnamed: R504.2, U501.23 (MODE1)
unnamed: R507.2, U501.24 (MS/MODE2)
unnamed: R510.2, U501.11 (OUTLN)
unnamed: R509.2, U501.10 (OUTLP)
unnamed: R511.2, U501.12 (OUTRN)
unnamed: R512.2, U501.13 (OUTRP)
unnamed: C509.1, U501.9 (VNEG)
unnamed: R508.2, U501.1 (XSMT)
unnamed: C525.1, U502.9 (AVDD)
unnamed: C534.2, U502.23 (BST_A)
unnamed: C536.2, U502.24 (BST_B)
unnamed: C535.2, U502.43 (BST_C)
unnamed: C537.2, U502.44 (BST_D)
unnamed: C524.2, U502.8 (C_START)
unnamed: R517.1, U502.16 (OC_ADJ)
unnamed: C536.1, L502.1, U502.32 (OUT_B)
unnamed: C535.1, L503.4, U502.35 (OUT_C)
unnamed: C538.2, U502.3 (VBG)
unnamed: C520.2, L501.2, U502.21 (VDD)
unnamed: C602.2, C604.2, R601.1, U601.14 (AVDD)
unnamed: C608.2, U601.8 (CAPM)
unnamed: C608.1, U601.6 (CAPP)
unnamed: R605.1, R606.2, U601.22 (GPIO2/ADR2/GPO)
unnamed: C607.1, U601.2 (LDOO)
unnamed: R602.1, R603.2, U601.32 (MISO(GPIO1)/ADR1/FMT)
unnamed: R604.2, U601.23 (MODE1)
unnamed: R607.2, U601.24 (MS/MODE2)
unnamed: R610.2, U601.11 (OUTLN)
unnamed: R609.2, U601.10 (OUTLP)
unnamed: R611.2, U601.12 (OUTRN)
unnamed: R612.2, U601.13 (OUTRP)
unnamed: C609.1, U601.9 (VNEG)
unnamed: R608.2, U601.1 (XSMT)
unnamed: C625.1, U602.9 (AVDD)
unnamed: C634.2, U602.23 (BST_A)
unnamed: C636.2, U602.24 (BST_B)
unnamed: C635.2, U602.43 (BST_C)
unnamed: C637.2, U602.44 (BST_D)
unnamed: C624.2, U602.8 (C_START)
unnamed: R617.1, U602.16 (OC_ADJ)
unnamed: C636.1, L602.1, U602.32 (OUT_B)
unnamed: C635.1, L603.4, U602.35 (OUT_C)
unnamed: C638.2, U602.3 (VBG)
unnamed: C620.2, L601.2, U602.21 (VDD)
unnamed: C702.2, C704.2, R701.1, U701.14 (AVDD)
unnamed: C708.2, U701.8 (CAPM)
unnamed: C708.1, U701.6 (CAPP)
unnamed: R705.1, R706.2, U701.22 (GPIO2/ADR2/GPO)
unnamed: C707.1, U701.2 (LDOO)
unnamed: R702.1, R703.2, U701.32 (MISO(GPIO1)/ADR1/FMT)
unnamed: R704.2, U701.23 (MODE1)
unnamed: R707.2, U701.24 (MS/MODE2)
unnamed: R710.2, U701.11 (OUTLN)
unnamed: R709.2, U701.10 (OUTLP)
unnamed: R711.2, U701.12 (OUTRN)
unnamed: R712.2, U701.13 (OUTRP)
unnamed: C709.1, U701.9 (VNEG)
unnamed: R708.2, U701.1 (XSMT)
unnamed: C725.1, U702.9 (AVDD)
unnamed: C734.2, U702.23 (BST_A)
unnamed: C736.2, U702.24 (BST_B)
unnamed: C735.2, U702.43 (BST_C)
unnamed: C737.2, U702.44 (BST_D)
unnamed: C724.2, U702.8 (C_START)
unnamed: R717.1, U702.16 (OC_ADJ)
unnamed: C736.1, L702.1, U702.32 (OUT_B)
unnamed: C735.1, L703.4, U702.35 (OUT_C)
unnamed: C738.2, U702.3 (VBG)
unnamed: C720.2, L701.2, U702.21 (VDD)
unnamed: C802.2, C804.2, R801.1, U801.14 (AVDD)
unnamed: C808.2, U801.8 (CAPM)
unnamed: C808.1, U801.6 (CAPP)
unnamed: R805.1, R806.2, U801.22 (GPIO2/ADR2/GPO)
unnamed: C807.1, U801.2 (LDOO)
unnamed: R802.1, R803.2, U801.32 (MISO(GPIO1)/ADR1/FMT)
unnamed: R804.2, U801.23 (MODE1)
unnamed: R807.2, U801.24 (MS/MODE2)
unnamed: R810.2, U801.11 (OUTLN)
unnamed: R809.2, U801.10 (OUTLP)
unnamed: R811.2, U801.12 (OUTRN)
unnamed: R812.2, U801.13 (OUTRP)
unnamed: C809.1, U801.9 (VNEG)
unnamed: R808.2, U801.1 (XSMT)
unnamed: C825.1, U802.9 (AVDD)
unnamed: C834.2, U802.23 (BST_A)
unnamed: C836.2, U802.24 (BST_B)
unnamed: C835.2, U802.43 (BST_C)
unnamed: C837.2, U802.44 (BST_D)
unnamed: C824.2, U802.8 (C_START)
unnamed: R817.1, U802.16 (OC_ADJ)
unnamed: C836.1, L802.1, U802.32 (OUT_B)
unnamed: C835.1, L803.4, U802.35 (OUT_C)
unnamed: C838.2, U802.3 (VBG)
unnamed: C820.2, L801.2, U802.21 (VDD)
unnamed: C902.2, C904.2, R901.1, U901.14 (AVDD)
unnamed: C907.2, U901.8 (CAPM)
unnamed: C907.1, U901.6 (CAPP)
unnamed: R906.1, R907.2, U901.22 (GPIO2/ADR2/GPO)
unnamed: C908.2, U901.2 (LDOO)
unnamed: R903.1, R904.2, U901.32 (MISO(GPIO1)/ADR1/FMT)
unnamed: R902.2, U901.23 (MODE1)
unnamed: R905.2, U901.24 (MS/MODE2)
unnamed: R912.2, U901.12 (OUTRN)
unnamed: R911.2, U901.13 (OUTRP)
unnamed: C909.1, U901.9 (VNEG)
unnamed: R908.1, U901.1 (XSMT)
unnamed: C919.2, R919.1, R920.2, U902.3 (+)
unnamed: C917.1, R917.2, R918.1, U902.2 (-)
unnamed: C918.1, C919.1, C922.1, R920.1, R921.1, R922.2, U902.5 (+)
unnamed: U902.6 (-), U902.7
unnamed: C1103.1, R1101.2, R1103.1, U1101.2 (-)
unnamed: C1104.1, R1104.1, R1105.1, U1101.6 (-)
unnamed: C1107.1, R1107.2, R1108.1, U1102.2 (-)
unnamed: C1108.1, R1109.1, R1110.1, U1102.6 (-)
unnamed: C1111.1, R1112.2, R1113.1, U1103.2 (-)
unnamed: C1112.1, R1114.1, R1115.1, U1103.6 (-)
unnamed: C1115.1, R1117.2, R1118.1, U1104.2 (-)
unnamed: C1116.1, R1119.1, R1120.1, U1104.6 (-)
unnamed: C1119.1, R1122.2, R1123.1, U1105.2 (-)
unnamed: C1120.1, R1124.1, R1125.1, U1105.6 (-)
unnamed: C1123.1, R1127.2, R1128.1, U1106.2 (-)
unnamed: C1124.1, R1129.1, R1130.1, U1106.6 (-)
unnamed: C1127.1, R1132.2, R1133.1, U1107.2 (-)
unnamed: C1128.1, R1134.1, R1135.1, U1107.6 (-)
unnamed: C1131.1, R1137.2, R1138.1, U1108.2 (-)
unnamed: C1132.1, R1139.1, R1140.1, U1108.6 (-)
unnamed: C1135.1, R1142.2, R1143.1, U1109.2 (-)
unnamed: C1136.1, R1144.1, R1145.1, U1109.6 (-)
unnamed: C1139.1, R1147.2, R1148.1, U1110.2 (-)
unnamed: C1140.1, R1149.1, R1150.1, U1110.6 (-)
unnamed: C1004.1, VR1001.1 (Boot)
unnamed: C1008.1, R1004.1, VR1001.6 (COMP)
unnamed: R1001.2, R1002.1, VR1001.3 (EN)
unnamed: R1005.2, R1006.1, VR1001.5 (FB)
unnamed: R1003.1, VR1001.4 (RT/CLK)
OSC-IOM: U404.4, U502.14 (OSC_IOM), U602.14 (OSC_IOM), U702.14 (OSC_IOM), U802.14 (OSC_IOM)
OSC-IOP: U402.13 (OSC_IOP), U403.4, U502.13 (OSC_IOP), U602.13 (OSC_IOP), U702.13 (OSC_IOP), U802.13 (OSC_IOP)
PVDD: C420.2, C421.2, C422.1, C423.2, C424.2, C425.1, C447.2, C448.2, C526.2, C527.2, C528.2, C529.2, C530.2, C531.2, C532.1, C533.1, C626.2, C627.2, C628.2, C629.2, C630.2, C631.2, C632.1, C633.1, C726.2, C727.2, C728.2, C729.2, C730.2, C731.2, C732.1, C733.1, C826.2, C827.2, C828.2, C829.2, C830.2, C831.2, C832.1, C833.1, C1001.1, C1002.1, C1003.1, C1005.1, C1006.1, R1001.1, TP1001.1, U402.29 (PVDD_AB), U402.30 (PVDD_AB), U402.31 (PVDD_AB), U402.36 (PVDD_CD), U402.37 (PVDD_CD), U402.38 (PVDD_CD), U502.29 (PVDD_AB), U502.30 (PVDD_AB), U502.31 (PVDD_AB), U502.36 (PVDD_CD), U502.37 (PVDD_CD), U502.38 (PVDD_CD), U602.29 (PVDD_AB), U602.30 (PVDD_AB), U602.31 (PVDD_AB), U602.36 (PVDD_CD), U602.37 (PVDD_CD), U602.38 (PVDD_CD), U702.29 (PVDD_AB), U702.30 (PVDD_AB), U702.31 (PVDD_AB), U702.36 (PVDD_CD), U702.37 (PVDD_CD), U702.38 (PVDD_CD), U802.29 (PVDD_AB), U802.30 (PVDD_AB), U802.31 (PVDD_AB), U802.36 (PVDD_CD), U802.37 (PVDD_CD), U802.38 (PVDD_CD), VR1001.2 (VIN)
SCK6: J901.17, R318.2, U901.26 (SCK)
SCL: J203.1, R235.2, TP214.1, TP250.1, TP254.1, U201.23 (UCB0SOMI/UCB0SCL/P3.1), U202.12 (SCL), U203.6 (SCL), U204.19 (SCL)
SCL1: R247.2, TP238.1, U204.2 (SC0)
SCL2: R245.2, TP240.1, U204.4 (SC1)
SCL3: R243.2, TP242.1, U204.6 (SC2)
SCL4: R241.2, TP244.1, U204.8 (SC3)
SCL5: R239.2, TP246.1, U204.11 (SC4)
SCL6: J901.16, JP902.1 (A), R237.2, TP248.1, U204.13 (SC5)
SDA: J203.2, R234.2, TP215.1, TP249.1, TP255.1, U201.22 (UCB0SIMO/UCB0SDA/P3.0), U202.13 (SDA), U203.5 (SDA), U204.20 (SDA)
SDA1: R248.2, TP237.1, U204.1 (SD0)
SDA2: R246.2, TP239.1, U204.3 (SD1)
SDA3: R244.2, TP241.1, U204.5 (SD2)
SDA4: R242.2, TP243.1, U204.7 (SD3)
SDA5: R240.2, TP245.1, U204.10 (SD4)
SDA6: J901.20, JP903.1 (A), R238.2, TP247.1, U204.12 (SD5)
SL+: C1103.2, J1111.12, R1103.2, R1104.2, U1101.1
SL-: C1104.2, J1111.14, R1105.2, U1101.7
SR+: C1123.2, C1124.2, J1111.16, R1128.2, R1129.2, R1130.2, U1106.1, U1106.7
UML+: C1107.2, C1108.2, J1111.20, R1108.2, R1109.2, R1110.2, U1102.1, U1102.7
UMR+: C1127.2, J1111.24, R1133.2, R1134.2, U1107.1
UMR-: C1128.2, J1111.26, R1135.2, U1107.7
VMID1: C1101.1, C1106.1, C1110.1, C1114.1, C1118.1, C1164.2, C1165.2, R1152.2, R1153.1, U1101.3 (+), U1101.5 (+), U1102.3 (+), U1102.5 (+), U1103.3 (+), U1103.5 (+), U1104.3 (+), U1104.5 (+), U1105.3 (+), U1105.5 (+)
VMID2: C1122.1, C1126.1, C1130.1, C1134.1, C1138.1, C1166.2, C1167.2, R1154.1, R1155.2, U1106.3 (+), U1106.5 (+), U1107.3 (+), U1107.5 (+), U1108.3 (+), U1108.5 (+), U1109.3 (+), U1109.5 (+), U1110.3 (+), U1110.5 (+)
/AMP-RESET1: R210.2, TP229.1, U202.2 (P0)
/AMP-RESET2: R211.2, TP230.1, U202.3 (P1)
/AMP-RESET3: R212.2, TP231.1, U202.4 (P2)
/AMP-RESET4: R213.2, TP232.1, U202.5 (P3)
/AMP-RESET5: R214.2, TP233.1, U202.7 (P4)

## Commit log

2025-05-21 Initial commit - ajout des deux projets KiCad
2025-06-09 Correction du nom de l'entreprise
2025-06-09 Mise à jour du schéma et ajout d'un nouveau projet
2025-06-09 Correction nom fichier
2025-10-09 Ajout du projet Ampli Audio Custom dans Amplificateur_Audio
2025-10-13 Assignation des empreintes des composants de la première page
2025-10-15 Ajout de l'assignation des compostants et des empreintes jusqu'à la page 6
2025-10-17 Assignation des composants et empreintes terminé
2025-10-21 Ajout de point de test et début du routage
2025-10-22 Modification d'empreinte et routage de sortie audio
2025-10-23 Continuation du routage
2025-10-24 suite du routage
2025-10-24 Suite routage
2025-10-28 Suite du placement
2025-10-28 Création d'une branche et changement de routage, PVDD passer en interne
2025-10-29 Suite du routage passage des sorties d'ampli en symétrique et même longueur
2025-10-29 Routage symétrique
2025-11-04 Amélioration du routage
2025-11-05 Suite amélioration du routage, PVDD local en top, et plan global couche 3. Passage des sorties audios OUTx en bottom
2025-11-06 Suite routage amélioré
2025-11-18 Placement casi définitif prochaine étape vias de GND + stitching
2025-12-09 Affinage du routage
2025-12-29 Routage finale pour Surround Channel, publication d'une backup avant clonage grace au multichannel
2025-12-30 Refactor : hierarchical template channels for multichannel routing
2025-12-30 Remove legacy channel schematics
2026-01-03 Factorisation réussite et validation de la duplication de channel
